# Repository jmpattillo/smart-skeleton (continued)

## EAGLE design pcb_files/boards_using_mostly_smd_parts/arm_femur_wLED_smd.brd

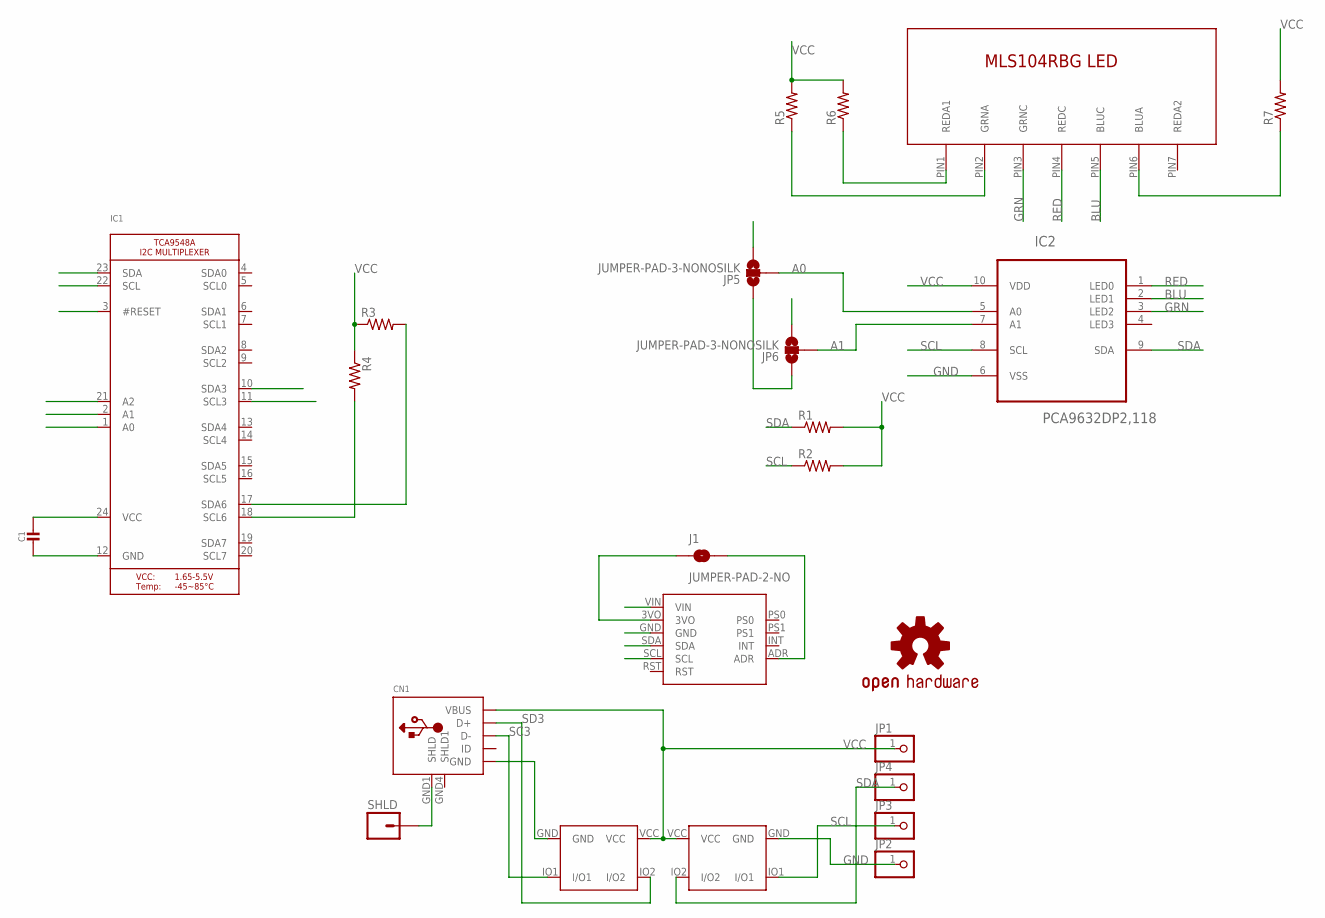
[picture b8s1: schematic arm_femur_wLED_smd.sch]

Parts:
C1: CAP_CERAMIC0805-NOTHERMALS; 0805_NOTHERMALS
CN1: USB; USB-MINIB-THM-MOLEX_NOSLK
IC1: TCA9548A; TSSOP24
IC2: PCA9632DP2,118; SOP50P490X110-10N
J1: JUMPER-PAD-2-NO; PAD-JUMPER-2-NO_NO_SILK
JP1, JP2, JP3, JP4: PINHD-1X1CB; 1X01-CLEANBIG
JP5, JP6: JUMPER-PAD-3-NONOSILK; PAD-JUMPER-3-NO_NO_SILK
LOGO1: OSHW-LOGOS; OSHW-LOGO-S
R1, R2, R3, R4, R5, R6, R7: RESISTOR0603-RES; 0603-RES
SHLD: M01PTH; 1X01
U$1: BNO_055_BKOUT; BNO_BKOUT
U$2: MSL0104RGB; 7-SMD
U$3, U$4: TVS_ARRAY_CD143A; SOT-143

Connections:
A0: IC2.5 (A0), JP5.2
A1: IC2.7 (A1), JP6.2
BLU: IC2.2 (LED1), U$2.PIN5 (BLUC)
GND: C1.2, CN1.GND, IC1.2 (A1), IC1.12 (GND), IC1.21 (A2), IC2.6 (VSS), JP2.1, JP5.1, JP6.1, U$1.GND, U$3.GND, U$4.GND
GRN: IC2.3 (LED2), U$2.PIN3 (GRNC)
unnamed: R6.1, U$2.PIN1 (REDA1)
unnamed: CN1.GND1 (SHLD), SHLD.1
unnamed: R5.1, U$2.PIN2 (GRNA)
unnamed: R7.1, U$2.PIN6 (BLUA)
unnamed: J1.1, U$1.3VO
unnamed: J1.2, U$1.ADR
RED: IC2.1 (LED0), U$2.PIN4 (REDC)
SC3: CN1.D-, IC1.11 (SCL3), U$4.IO1 (I/O1)
SC6: IC1.18 (SCL6), R4.2, U$1.SCL
SCL: IC1.22 (SCL), IC2.8 (SCL), JP3.1, R2.1, U$3.IO1 (I/O1)
SD3: CN1.D+, IC1.10 (SDA3), U$4.IO2 (I/O2)
SD6: IC1.17 (SDA6), R3.2, U$1.SDA
SDA: IC1.23 (SDA), IC2.9 (SDA), JP4.1, R1.1, U$3.IO2 (I/O2)
VCC: C1.1, CN1.VBUS, IC1.1 (A0), IC1.3 (#RESET), IC1.24 (VCC), IC2.10 (VDD), JP1.1, JP5.3, JP6.3, R1.2, R2.2, R3.1, R4.1, R5.2, R6.2, R7.2, U$1.VIN, U$3.VCC, U$4.VCC

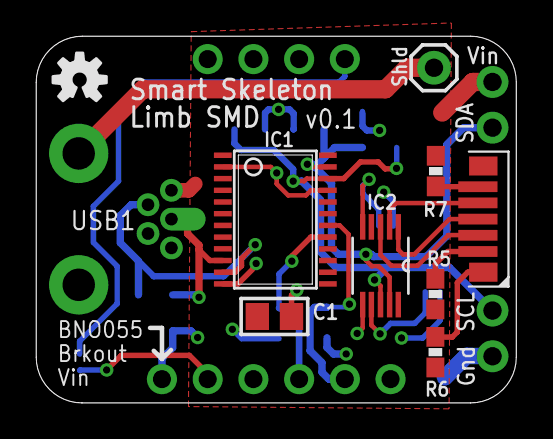
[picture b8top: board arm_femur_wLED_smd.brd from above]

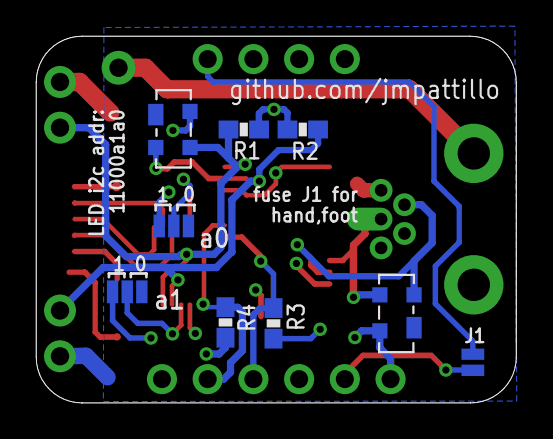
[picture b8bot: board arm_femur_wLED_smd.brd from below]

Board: 2 copper layers, 26.7 x 20.4 mm, 24 parts (9 on the bottom side), 19 nets.

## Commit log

2019-05-17 Create empty
2019-05-17 Added case files
2019-05-18 added f3d archive files for cases
2019-05-18 uploaded pcb files
2019-05-18 updated directory names
2019-05-19 uploaded main case model
2019-10-14 Delete LICENSE
    Changing to CC share alike license
2019-10-15 Added application files
    Added Unity Project folder, builds for OSX and Win64, spreadsheet files, and arduino code
2019-10-16 zipped application files
2021-02-17 uploaded new builds
2021-02-17 Re-uploaded unity project directory
2021-02-18 revised arduino code
2021-02-20 added altered BNO055 library
2021-02-25 updated spreadsheet files
2021-02-27 upgraded unity project
    Upgraded Unity project to 2019.4.21f1
    Added ability to put commas in questions.csv fields by substituting a
    "|" for a comma
2021-02-27 reuploading objects that were on icloud
2021-02-27 reupload small unity file
2021-05-05 Fixed bug in application files
    Fixed bug preventing commas from working in function descriptions. Added quit and reset buttons
2021-05-05 added update log
2021-05-13 Added Bill of Materials
2021-05-13 added pcb files for new led daughter board.
2021-05-13 Updated log
2021-05-23 added spine bracket
2021-05-27 Added assembly document
